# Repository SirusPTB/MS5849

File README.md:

Unlock Precision with the MS5849 PCB – with JST Connector
Take your pressure sensing to the next level with the MS5849, a 
high-resolution digital pressure sensor mounted on a compact, 
ready-to-integrate PCB with JST connector for hassle-free plug-and-play 
installation. Whether you're prototyping drones, robotics, or IoT devices, 
this board delivers ultra-accurate barometric and temperature readings 
in a rugged, reliable format. The JST connector ensures quick 
connectivity with minimal wiring — ideal for tight builds and rapid
development cycles.

Key Benefits:

High-precision digital pressure + temperature sensor

Plug-and-play JST connector for rapid integration

Compact, robust PCB layout

Perfect for drones, weather stations, and embedded systems

Get reliable data, faster setup, and cleaner builds — all in one tiny board.

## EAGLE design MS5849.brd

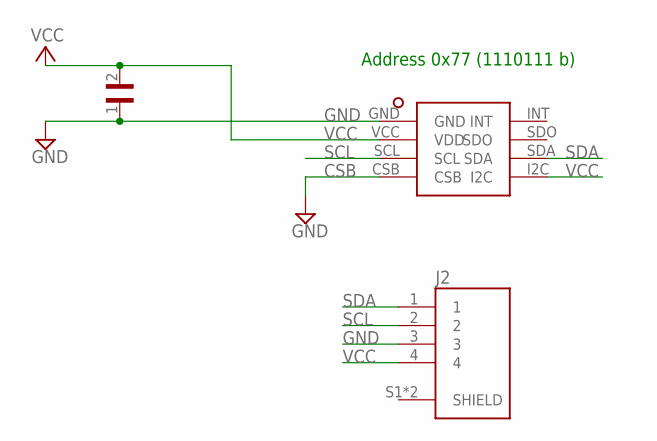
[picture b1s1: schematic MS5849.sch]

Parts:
C2: CC0603KRX7R9BB104; CAPC1608X90
J2: B4B-ZR-SM4-TFT(LF)(SN); JST_B4B-ZR-SM4-TFT(LF)(SN)
U$2: MS5849-30B; MS5849-30B-FOOTPRINT

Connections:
CSB: U$2.CSB
GND: C2.1, J2.3, U$2.GND
SCL: J2.2, U$2.SCL
SDA: J2.1, U$2.SDA
VCC: C2.2, J2.4, U$2.I2C, U$2.VCC (VDD)

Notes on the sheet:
Address 0x77 (1110111 b)

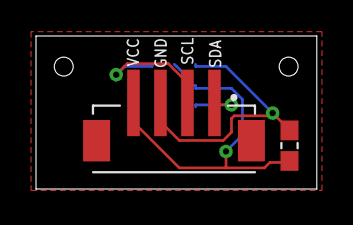
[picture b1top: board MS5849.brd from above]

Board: 2 copper layers, 15.6 x 8.5 mm, 3 parts (1 on the bottom side), 4 nets.

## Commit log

2025-04-26 README.md
